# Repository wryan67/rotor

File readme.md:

Antenna Rotor Controller
------------------------
This program is designed to work with any rotor that uses a variable resistor for it's aspect indicator and limit swithes to prevent turning past the starting/stopping point.  Checkout the readme folder for display pinouts and a [[circuit diagram]](https://raw.githubusercontent.com/wryan67/rotor/main/schematics/drawio/rotor.png) for the system.

A special thanks to [PCBWay.com](http://www.pcbway.com) for supplying the professionally made PCB board!  

### Rotor Aspect Indicator
This system was designed around, and tested using a "Tail Twister" Model T2X - Rotator.  The Tail Twister utilizes a 500Ω variable resistor to ascertain the antenna's current direction.  The 500Ω variable resistor looks like this:  

### Prerequisites:

Required system Libraries:

    $ sudo apt install libgtk-3-dev glade xdotool gawk ksh

Optional system Libraries:

    $ sudo apt vim tigervnc-standalone-server  tigervnc-xorg-extension tigervnc-scraping-server

## WiringPi

This step is required on RPi 4B.   Follow the instrctions on this website to upgrade to version 2.52

* http://wiringpi.com/wiringpi-updated-to-2-52-for-the-raspberry-pi-4b/

## Configuration

Using raspi-config, these options can be manuplated.  Enabling the I2C and SPI busses are required.

* System Options
  * Set the hostname
  * Set the pasword for the pi user
* Display Options
  * Disable screen blanking
* Interface Options
  * Enable the I2C bus
  * Enable the SPI bus
  * Enable the VNC server
  * Enable the SSH server

Starting raspi-config:

    $ sudo raspi-config

## Requirements

Overclocking the I2C bus is required to achive the desired 2500 samples per second.  Edit the /boot/config.txt file using:

Note: this step may need to be reapeated after installing a display device driver

    $ sudo vi /boot/config.txt 

Next, look for the i2c_arm parameter.  Note that if you've already enable the i2c bus via raspi-config, then you may have multiple lines in the config.txt file that have i2c_arm.  Look for the one that is uncommented.   If there are multiple "dtparam=i2c_arm=on" lines that are uncommented, comment out all but one.

    #dtparam=i2c_arm=on
    - or -
    dtparam=i2c_arm=on

Change it to:

    dtparam=i2c_arm=on,i2c_arm_baudrate=400000

## Disable warning lights
While you're in the boot config, you may want to disable the power indicator and lightning bolt indicator.  These indicators do not work properly on older RPi models due to an under sized capacitor on the RPi.  Newer models have larger capacitors, so if you have a brand new RPi 4, this step may not be necessary, but for the older RPi 4's, this indicator is extremely annoying. 

    $ sudo vi /boot/config.txt
    
    Append the following lines:
    
    # only affects power led operation
    dtparam=pwr_led_trigger=none
    dtparam=pwr_led_activelow=off
    # affects lightning bolt indicator
    avoid_warnings=1

### Required GIT Hub software:

Pleaase read the installation instructions carefully on each github project.  They're all similar, but non necessarially the same. 

* ADS1115 Library - https://github.com/wryan67/ads1115_rpi_lib    

      $ git clone https://github.com/wryan67/ads1115_rpi_lib.git

* NeoPixel Library - https://github.com/wryan67/neopixel_rpi_lib

       $ git clone https://github.com/wryan67/neopixel_rpi_lib.git       

* Log4Pi -https://github.com/wryan67/log4pi

       $ git clone https://github.com/wryan67/log4pi.git

### Download:

    git clone https://github.com/wryan67/rotor.git
    
### Compile:

    $ make
    
### Run:

Follow the instructions for autostart, then setup
    $ . scripts/set
    $ ./bin/rotor
    
### Auto Start on Boot

To start rotor on boot:

* Copy all files from the scripts folder (in this project) to $HOME/bin, then setup lxsession autostart using these commands:

      $ mkdir -p /home/pi/bin
      $ cp -p /home/pi/rotor/scripts/* /home/pi/bin
      $ cp -p /home/pi/rotor/bin/rotor /home/pi/bin
      $ cd /home/pi/bin
      $ sudo chown root rotor
      $ sudo chmod g+w  rotor
      $ sudo chmod u+s  rotor
      $ sudo chmod a+x  rotor
      $ mkdir -p ~/.config/lxsession/LXDE-pi/
      $ ln /home/pi/bin/autostart ~/.config/lxsession/LXDE-pi/autostart

### Build

This is the 2nd controller I built:

### Screenshots:

In order to access the configuration screens, click anywhere on the time clock.

## Parts list
 
[Parts List](https://docs.google.com/spreadsheets/d/144g_11gsdxmeO28szwi-ss_1HRNR7ysNT9Fy6vf18YI/edit?usp=sharing)

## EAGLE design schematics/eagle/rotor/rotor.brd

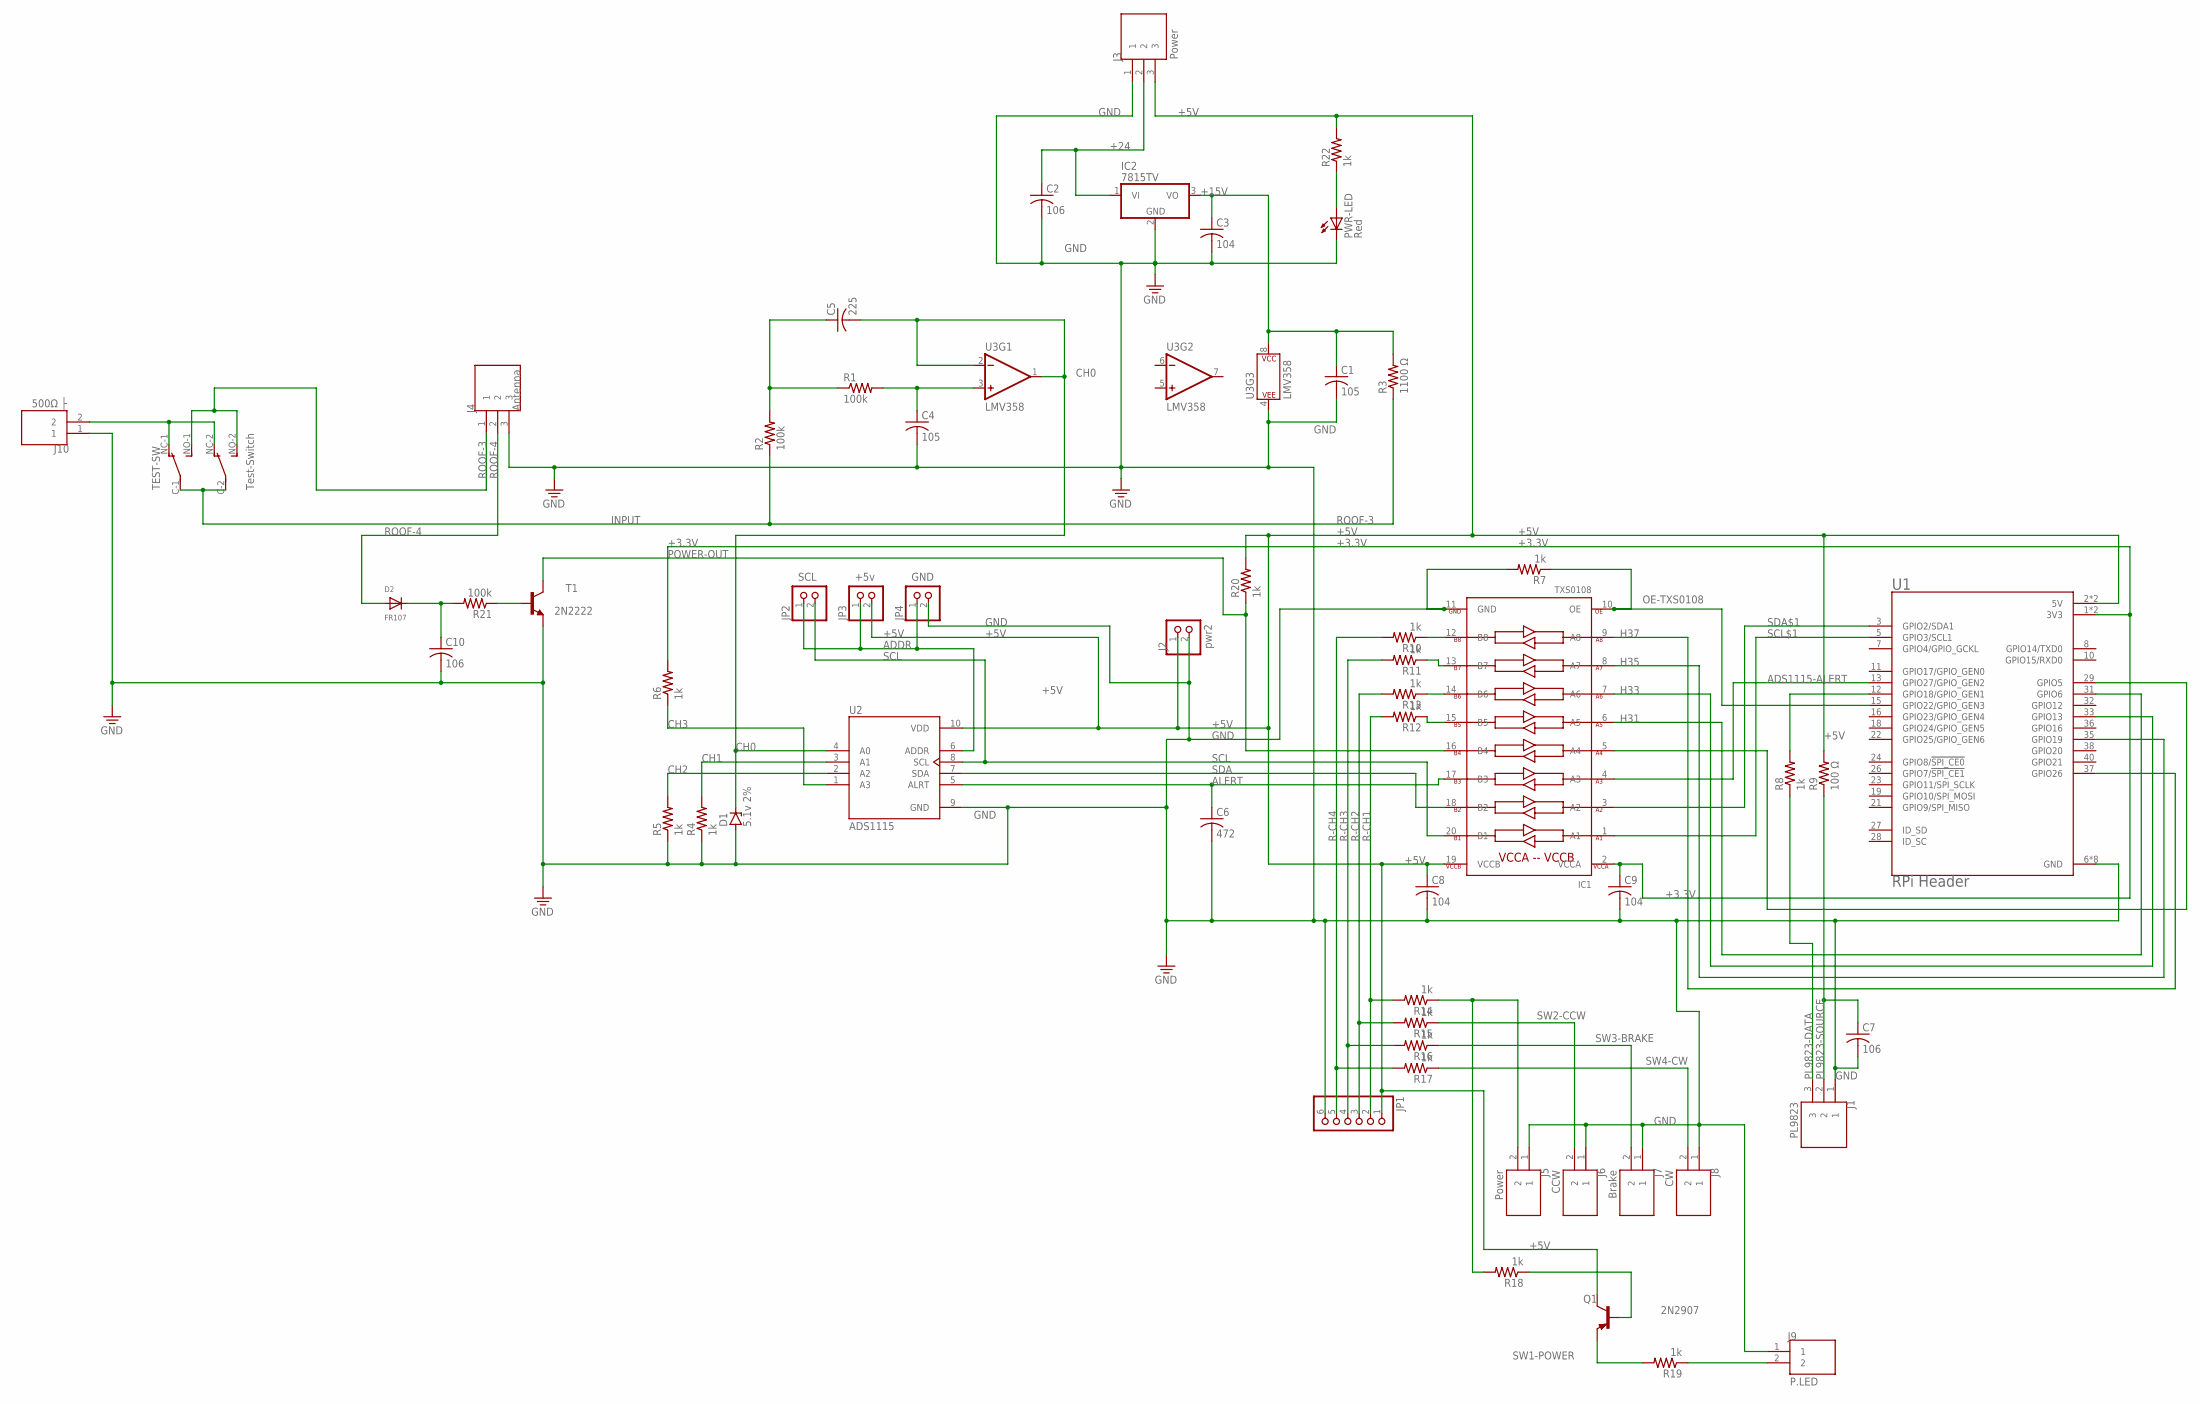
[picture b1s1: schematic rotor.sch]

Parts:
C1, C4: 105; C0805
C2, C7, C10: 106; C0805
C3, C8, C9: 104; C0805
C5: 225; C0805
C6: 472; C0805
D1: 5.1v 2%; ZDIO-7.5
D2: FR107; SMADIODE
IC1: TXS0108; TSSOP20
IC2: 7815TV; TO220V
J1: PL9823; CUI_TB004-508-03BE
J2: pwr2; 1X02
J3: Power; CUI_TB004-508-03BE
J4: Antenna; CUI_TB004-508-03BE
J5: Power; CUI_TB004-508-02BE
J6: CCW; CUI_TB004-508-02BE
J7: Brake; CUI_TB004-508-02BE
J8: CW; CUI_TB004-508-02BE
J9: P.LED; CUI_TB004-508-02BE
J10: 500Ω ├; CUI_TB004-508-02BE
JP1: PINHD-1X6; 1X06
JP2: SCL; 1X02-SPECIAL
JP3: +5v; 1X02-SPECIAL
JP4: GND; 1X02-SPECIAL
PWR-LED: Red; CHIP-LED0805
Q1: 2N2907; TO92-EBC-OVAL
R1, R2, R21: 100k; M0805
R3: 1100 Ω; M0805
R4, R5, R6, R7, R8, R10, R11, R12, R13, R14, R15, R16, R17, R18, R19, R20, R22: 1k; M0805
R9: 100 Ω; M0805
T1: 2N2222; TO92-EBC-OVAL
TEST-SW: Test-Switch; DP-DT
U1: RPi Header; MODULE_RASPBERRY_PI_3B+_HDR
U2: ADS1115; MODULE_1115_NARROW
U3: LMV358; SO08

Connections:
+3.3V: C9.1, IC1.2 (VCCA), R6.2, U1.1 (3V3), U1.17 (3V3)
+5V: C8.1, IC1.19 (VCCB), J2.1, J3.3, JP1.1, JP3.2, Q1.C, R9.2, R20.2, R22.2, U1.2 (5V), U1.4 (5V), U2.10 (VDD)
+15V: C1.1, C3.1, IC2.3 (VO), R3.2, U3.8 (P$V+)
+24: C2.1, IC2.1 (VI), J3.2
ADDR: JP2.1, JP3.1, JP4.1, U2.6 (ADDR)
ADS1115-ALERT: IC1.4 (A3), U1.13 (GPIO27/GPIO_GEN2)
ALERT: C6.1, IC1.17 (B3), U2.5 (ALRT)
CH0: C5.2, D1.C, U2.4 (A0), U3.1 (OUT), U3.2 (-IN)
CH1: R4.2, U2.3 (A1)
CH2: R5.2, U2.2 (A2)
CH3: R6.1, U2.1 (A3)
GND: C1.2, C2.2, C3.2, C4.2, C6.2, C7.2, C8.2, C9.2, C10.2, D1.A, IC1.11 (GND), IC2.2 (GND), J1.1, J2.2, J3.1, J4.3, J5.1, J6.1, J7.1, J8.1, J9.1, J10.1, JP1.6, JP4.2, PWR-LED.C, R4.1, R5.1, R7.2, T1.E, U1.6 (GND), U1.9 (GND), U1.14 (GND), U1.20 (GND), U1.25 (GND), U1.30 (GND), U1.34 (GND), U1.39 (GND), U2.9 (GND), U3.4 (P$V-)
H31: IC1.6 (A5), U1.31 (GPIO6)
H33: IC1.7 (A6), U1.33 (GPIO13)
H35: IC1.8 (A7), U1.35 (GPIO19)
H37: IC1.9 (A8), U1.37 (GPIO26)
INPUT: R2.1, R3.1, TEST-SW.C-1, TEST-SW.C-2
unnamed: C4.1, R1.2, U3.3 (+IN)
unnamed: R8.2, U1.12 (GPIO18/GPIO_GEN1)
unnamed: C5.1, R1.1, R2.2
unnamed: IC1.15 (B5), R12.1
unnamed: IC1.14 (B6), R13.1
unnamed: IC1.13 (B7), R11.1
unnamed: IC1.12 (B8), R10.1
unnamed: Q1.E, R19.2
unnamed: Q1.B, R18.1
unnamed: IC1.5 (A4), U1.29 (GPIO5)
unnamed: C10.1, D2.C, R21.2
unnamed: R21.1, T1.B
unnamed: PWR-LED.A, R22.1
unnamed: J10.2, TEST-SW.NC-1, TEST-SW.NC-2
OE-TXS0108: IC1.10 (OE), R7.1, U1.15 (GPIO22/GPIO_GEN3)
PL9823-DATA: J1.3, R8.1
PL9823-SOURCE: C7.1, J1.2, R9.1
POWER-OUT: IC1.16 (B4), R20.1, T1.C
R-CH1: JP1.2, R12.2, R14.2
R-CH2: JP1.3, R13.2, R15.2
R-CH3: JP1.4, R11.2, R16.2
R-CH4: JP1.5, R10.2, R17.2
ROOF-3: J4.1, TEST-SW.NO-1, TEST-SW.NO-2
ROOF-4: D2.A, J4.2
ROTOR-PWR-LED-SOURCE: J9.2, R19.1
SCL: IC1.20 (B1), JP2.2, U2.8 (SCL)
SCL$1: IC1.1 (A1), U1.5 (GPIO3/SCL1)
SDA: IC1.18 (B2), U2.7 (SDA)
SDA$1: IC1.3 (A2), U1.3 (GPIO2/SDA1)
SW1-POWER: J5.2, R14.1, R18.2
SW2-CCW: J6.2, R15.1
SW3-BRAKE: J7.2, R16.1
SW4-CW: J8.2, R17.1

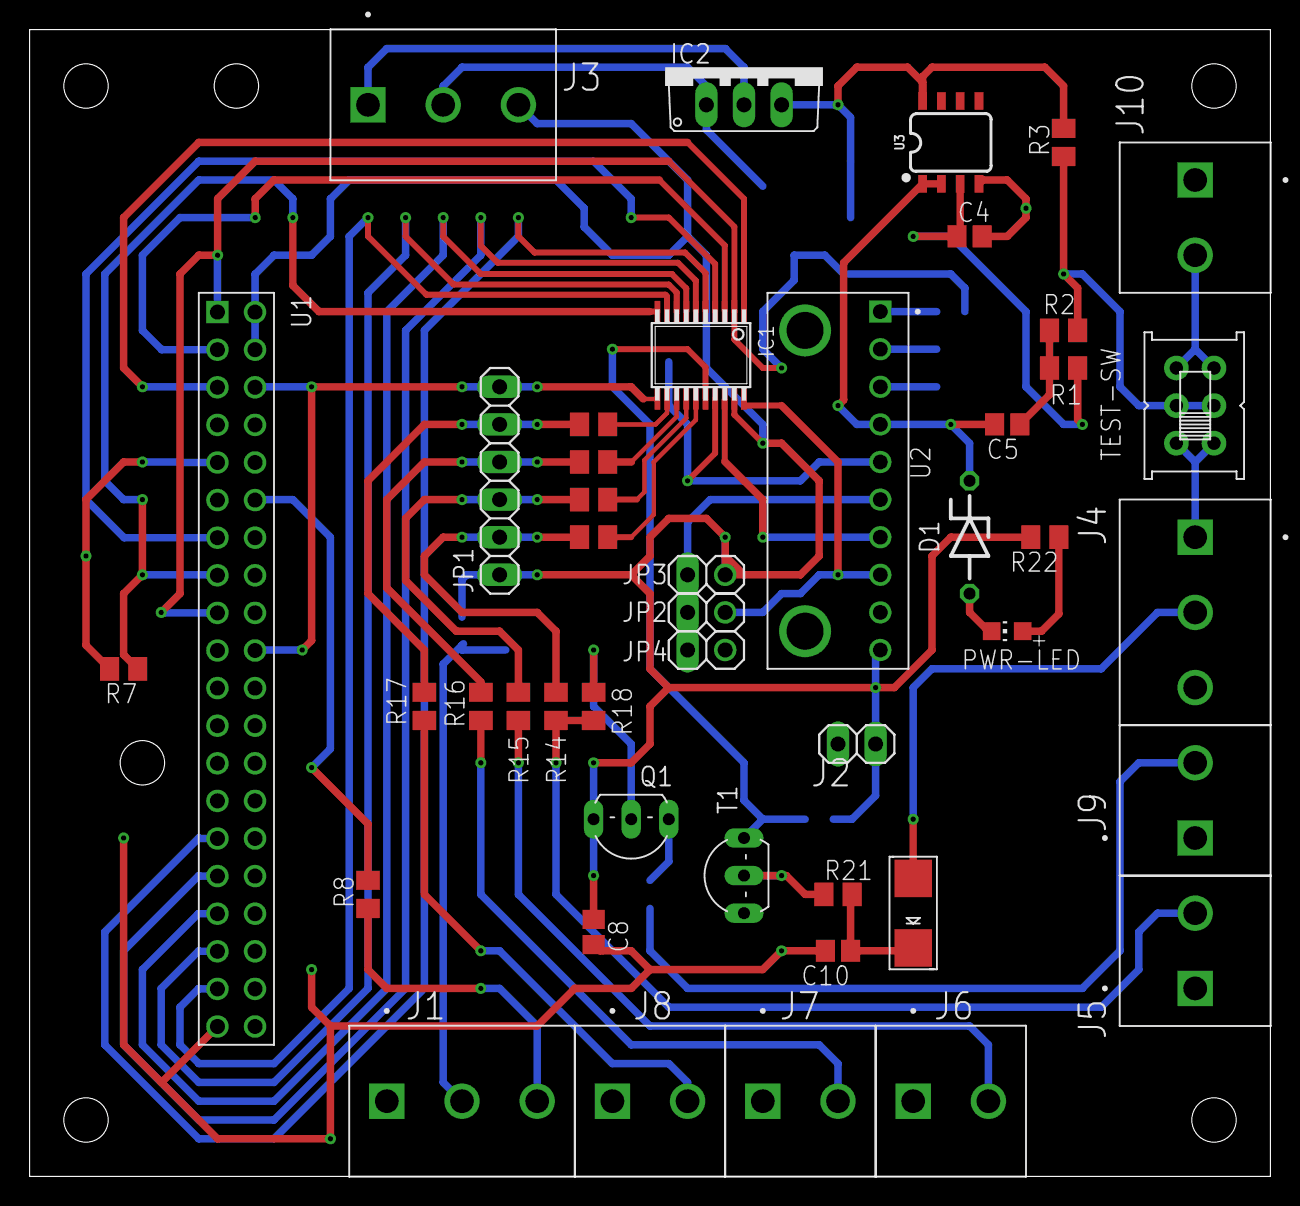
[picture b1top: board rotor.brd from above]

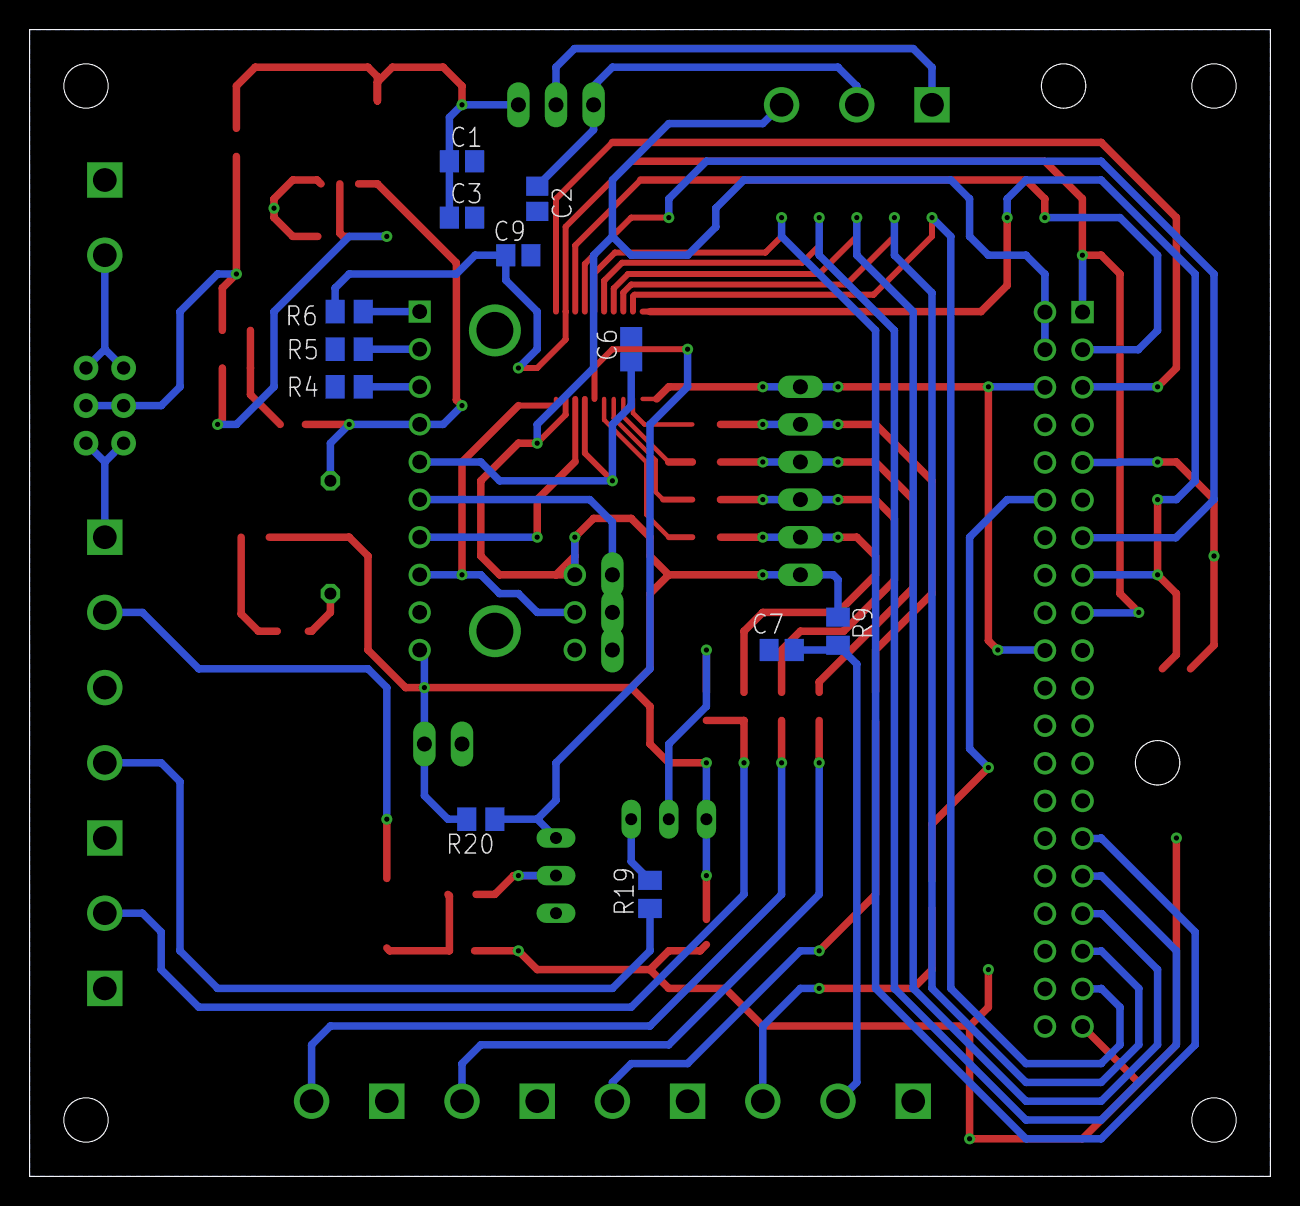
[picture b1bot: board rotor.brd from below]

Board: 2 copper layers, 83.8 x 77.5 mm, 57 parts (12 on the bottom side), 50 nets.

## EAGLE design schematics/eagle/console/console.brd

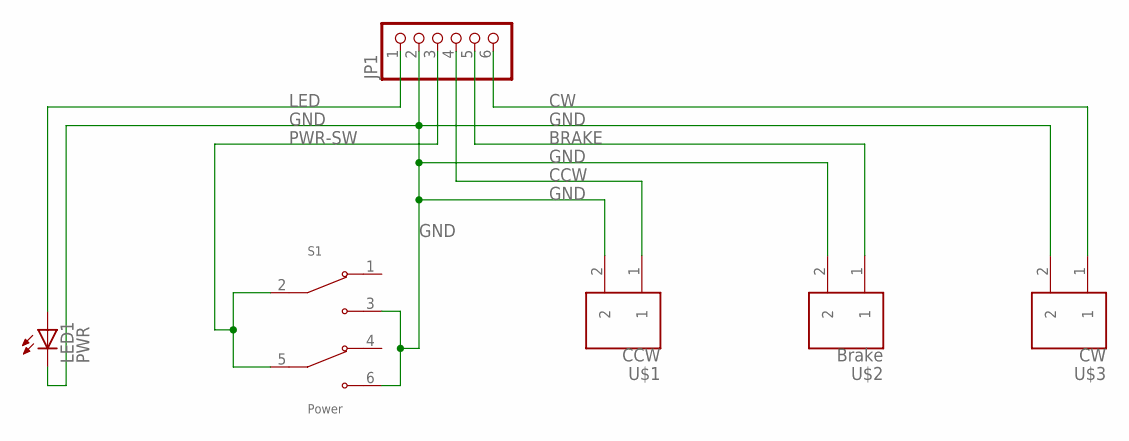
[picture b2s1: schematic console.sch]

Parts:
JP1: PINHD-1X6; 1X06
LED1: PWR; CHIPLED_0805
S1: Power; IM211
U$1: CCW; SPST-5MM
U$2: Brake; SPST-5MM
U$3: CW; SPST-5MM

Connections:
BRAKE: JP1.5, U$2.1
CCW: JP1.4, U$1.1
CW: JP1.6, U$3.1
GND: JP1.2, LED1.C, S1.3 (NO1), S1.6 (NO2), U$1.2, U$2.2, U$3.2
LED: JP1.1, LED1.A
PWR-SW: JP1.3, S1.2 (COM1), S1.5 (COM2)

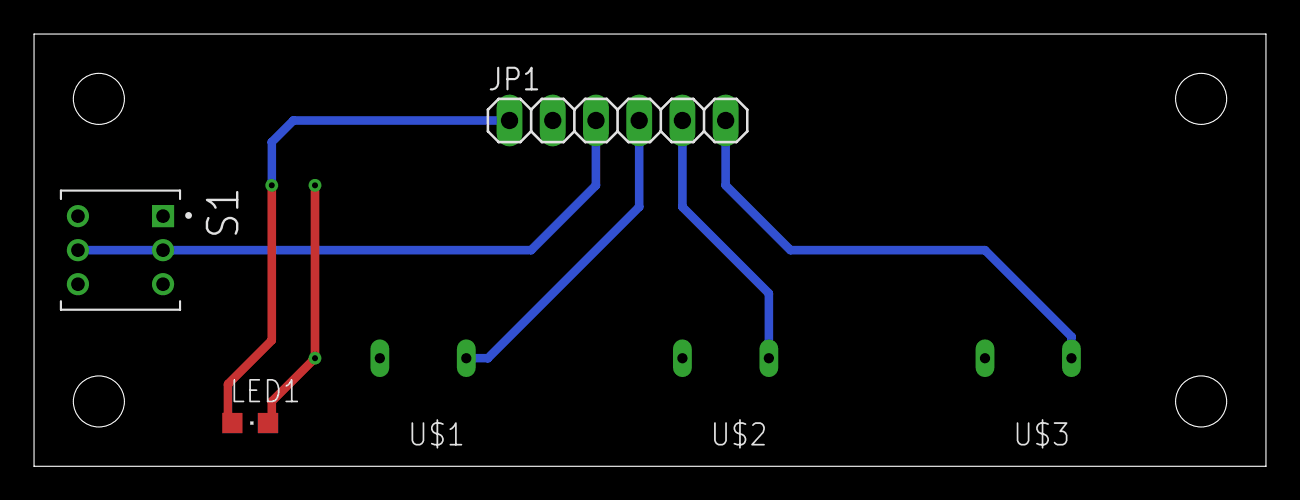
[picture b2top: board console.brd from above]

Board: 2 copper layers, 72.4 x 25.4 mm, 6 parts (0 on the bottom side), 6 nets.

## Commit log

2020-11-30 initial
2020-11-30 adjust arrow size
2020-11-30 fix render compass
2020-11-30 alpha directions
2020-11-30 update decimal degree input
2020-11-30 add lock for update text
2020-11-30 fix text box locking
2020-11-30 update comments
2020-11-30 added fast moves
2020-11-30 updated move rotor
2020-11-30 rotor
2020-11-30 fix compass background transparency
2020-12-01 added style sheet
2020-12-01 add fullscreen option
2020-12-01 added directional buttons
2020-12-29 mcp3008
2020-12-31 multi-threaded gtk
2020-12-31 wobble limit
2020-12-31 move rotor diagnosits
2020-12-31 adjust motor controll
2020-12-31 prevent duplicate movements
2020-12-31 adjust increment buttons to match wobble limit
2020-12-31 fix 100% cpu usage
2020-12-31 new engine code for actual rotor
2020-12-31 separate rotor Vs from mcp3008 reference voltage
2021-01-01 degree translations
2021-01-01 update engine relay states
2021-01-02 basic functionality
2021-01-02 miscellaneous debugging improvements
2021-01-02 sliding window moving average
2021-01-03 move sync strategy to motor.cpp & added command line parameter for selecting channel
2021-01-04 misc.
2021-01-05 add neopixel for operation status
2021-01-06 circuit diagram
2021-01-06 readme
2021-01-06 layout adjustment
2021-01-07 update resistor values
2021-01-07 update circuit diagram
2021-01-07 update circuit diagram title
2021-01-07 add options for a2c channels and resistors
2021-01-09 adjust for static
2021-01-09 calibration
2021-01-10 linear slope
2021-01-10 linar slope
2021-01-10 add 24v relay to circuit digram
2021-01-10 twilight zone
2021-01-10 misc. visual improvements
2021-01-10 misc. visual enhancements
2021-01-10 screenshots
2021-01-10 rotor.png
2021-01-12 made the pins on I2C LLC match the physical device
2021-04-05 updated parking brake debug statements
2021-04-18 fix boot flap
2021-04-18 publish update
2021-04-18 init pins
2021-04-19 external power
2021-04-25 unknown
2021-04-25 15v working
2021-04-26 added rotor power
2021-04-26 add bcm/hdr pinout numbers to source enum "RotorPin"
2021-04-30 circuit_diagram
2021-05-07 update pins & formulas
2021-05-08 tests
2021-05-08 trap interrupt
2021-05-08 4-inch-display
2021-05-08 script-update
2021-05-08 scripts
2021-05-09 working-2021-05-08
2021-05-09 max volts adjustment
2021-05-09 reorg
2021-05-09 script updates
2021-05-09 scripts update
2021-05-09 remove slope
2021-05-09 compass updates
2021-05-09 autostart
2021-05-09 neopixel fix
2021-05-09 make clean
2021-05-09 move mouse on boot
2021-05-10 fix power issue
2021-05-10 new screenshot
2021-05-10 time updates
2021-05-10 hide-mouse
2021-05-11 abort button
2021-05-15 Add files via upload
    500 ohm aspect indicator variable resistor
2021-05-21 build
2021-05-23 color codes
2021-05-25 read voltage update
2021-05-27 continuous read mode
2021-05-27 window size updates
2021-05-27 fine tune sample period
2021-05-28 add retries
2021-05-29 display degree on compass
2021-05-29 settings dialogue
2021-05-29 settings
2021-05-30 timezone
2021-05-31 time zone
2021-05-31 timezone scroll
2021-05-31 timezone working
2021-05-31 timezones working well
2021-05-31 hide mouse
2021-05-31 timezone beautify
2021-06-01 test updates
2021-06-06 new resistor value & gain
2021-06-07 cable disconnected dialog
2021-06-07 add skip window to smooth starts
2021-06-07 better disconnect message
2021-06-07 boot error window
2021-06-07 boot error
2021-06-07 boot errors
2021-06-07 beautify error messages
2021-06-07 hide mouse on boot error
2021-06-07 settings click isolated to clock
2021-06-07 fixed braking stop color delay
2021-06-07 more boot errors
2021-06-07 fix timezone min height for small screens
2021-06-09 shorten target window
2021-06-12 wifi settings
2021-06-13 wifi setttings
2021-06-13 small screen layout adjustment
2021-06-13 beautify
2021-06-14 intenet detection
2021-06-14 regorg
2021-06-14 fix show realized ip delay
2021-06-14 realized ip disappearance fixed
2021-06-14 timzone speedup
2021-06-14 fix ssid selection tab change
2021-06-14 fine tune wifi list-box
2021-06-18 parts-list
2021-06-19 wifi freq update
2021-06-19 wifi frequency update
2021-06-20 calibration screen
2021-06-21 boot override
2021-06-21 thread neopixel color test
2021-06-21 fix button aspect ratio
2021-06-21 better message window
2021-07-03 run.sh
2021-07-04 publish localhost
2021-07-04 move parts list to google sheets
2021-09-26 display pinout update
2021-09-26 display updates
2021-09-26 deploy.sh
2021-09-27 p9823-F5 pinout
2021-09-27 limit switch detection update
2021-09-27 new photos
2021-09-28 build photos
2021-09-29 limit switch detection circuit scope screenshots
2021-10-16 low pass filter wire diagram
2021-10-17 update circuit diagram - ads1115 alert ready
2021-10-17 change default resistor
2021-10-17 fix update wifi script
2022-10-01 print resistor values
2023-02-27 rotor manual
2023-03-03 crontab
2023-03-04 eagle cad
2023-03-05 eagle-initial version
2023-03-05 eagle
2023-03-05 add dpdt switch
2023-03-17 rotor v1.01
2023-03-18 fix rotor input resistor
2023-03-18 labels
2023-03-18 v1.02 - fix transistors
2023-03-19 redo sps calculator
2023-03-19 busy on boot message
2023-03-19 increased sps to max of 860
2023-10-08 2n2222 diagram

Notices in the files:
parts and their libraries:
SparkFun-IC-Amplifiers: Licensing: Creative Commons ShareAlike 4.0 International - https://creativecommons.org/licenses/by-sa/4.0
